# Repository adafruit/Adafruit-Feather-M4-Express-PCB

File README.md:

## Adafruit Feather M4 Express microcontroller board PCB

<a href="http://www.adafruit.com/products/3857"><br/>
Click here to purchase one from the Adafruit shop</a>

PCB files for the Adafruit Feather M4 Express. PCB format is EagleCAD schematic and board layout

For more details, check out the product pages at
* https://www.adafruit.com/products/3857

### Description

It's what you've been waiting for, the Feather M4 Express featuring ATSAMD51. This Feather is fast like a swift, smart like an owl, strong like a ox-bird (it's half ox, half bird, OK?) This feather is powered by our new favorite chip, the ATSAMD51J19 -  with its 120MHz Cortex M4 with floating point support and 512KB Flash and 192KB RAM. Your code will zig and zag and zoom, and with a bunch of extra peripherals for support, this will for sure be your favorite new chipset.

And best of all, it's a Feather - so you know it will work with all our FeatherWings! What a great way to quickly get up and running.

The most exciting part of the Feather M4 is that while you can use it with the Arduino IDE - and it's bonkers fast when you do, we are shipping it with CircuitPython on board. When you plug it in, it will show up as a very small disk drive with main.py on it. Edit main.py with your favorite text editor to build your project using Python, the most popular programming language. No installs, IDE or compiler needed, so you can use it on any computer, even ChromeBooks or computers you can't install software on. When you're done, unplug the Feather and your code will go with you.

### License

Adafruit invests time and resources providing this open source design, please support Adafruit and open-source hardware by purchasing products from [Adafruit](https://www.adafruit.com)!

Designed by Limor Fried/Ladyada for Adafruit Industries.

Creative Commons Attribution/Share-Alike, all text above must be included in any redistribution. See license.txt for additional details.

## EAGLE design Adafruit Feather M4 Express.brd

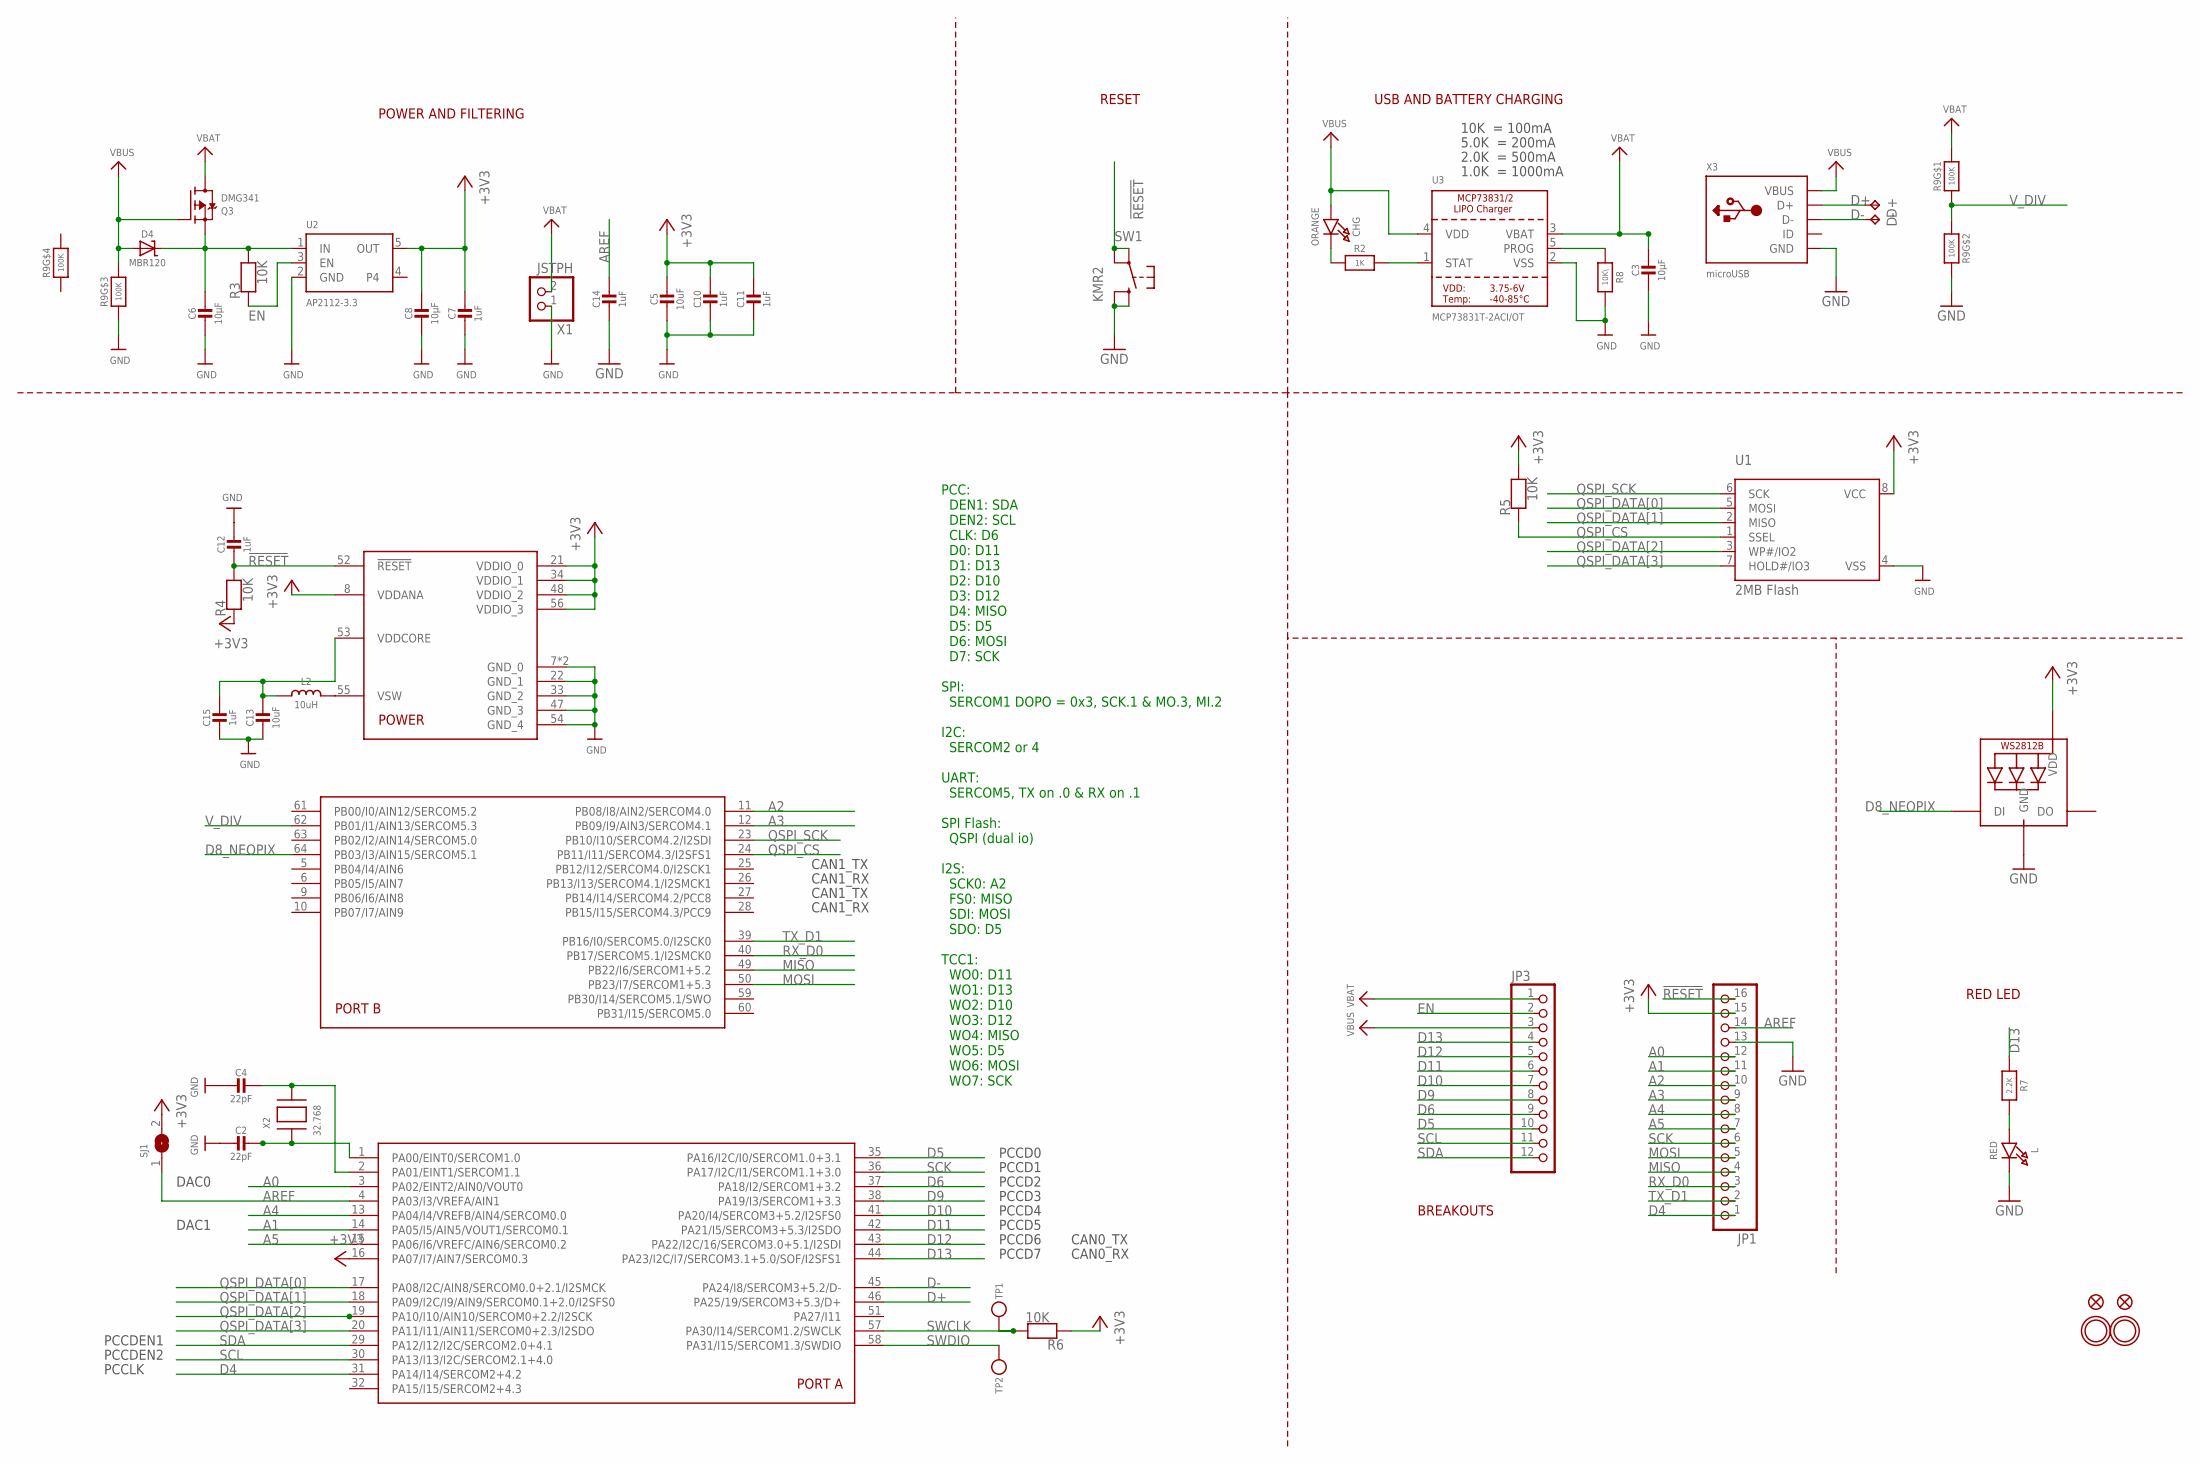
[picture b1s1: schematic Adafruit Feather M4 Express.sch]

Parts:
C2, C4: 22pF; 0603-NO
C3, C6, C8: 10µF; 0805-NO
C5, C13: 10uF; 0805-NO
C7, C10, C11, C12, C14, C15: 1uF; 0603-NO
CHG: ORANGE; CHIPLED_0805_NOOUTLINE
D4: MBR120; SOD-123
D+: TPB1,27; B1,27
D-: TPB1,27; B1,27
JP1: HEADER-1X16ROUND; 1X16_ROUND
JP3: HEADER-1X12; 1X12_ROUND
L: RED; CHIPLED_0805_NOOUTLINE
L2: 10uH; INDUCTOR_1007
LED1: WS2812B3535; LED3535
Q3: DMG341; SOT23-R
R2: 1K; 0603-NO
R3, R4, R5, R6: 10K; 0603-NO
R7: 2.2K; 0603-NO
R8: 10K\; 0603-NO
R9: 100K; RESPACK_4X0603_NO
SJ1: SOLDERJUMPERCLOSED; SOLDERJUMPER_CLOSEDWIRE
SW1: KMR2; BTN_KMR2_4.6X2.8
TP1, TP2: TESTPOINTROUND1.5MM; TESTPOINT_ROUND_1.5MM
U1: 2MB Flash; USON8
U2: AP2112-3.3; SOT23-5
U3: MCP73831T-2ACI/OT; SOT23-5
U$14: ATSAMD51J; PQFN64-1
U$31, U$32: MOUNTINGHOLE2.5; MOUNTINGHOLE_2.5_PLATED
U$34, U$35: FIDUCIAL_1MM
X1: JSTPH; JSTPH2
X2: 32.768; XTAL3215
X3: microUSB; 4UCONN_20329_V2

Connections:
!RESET: C12.2, JP1.16, R4.2, SW1.A, SW1.A' (P1), U$14.52 (!RESET)
+3V3: C5.1, C7.1, C8.1, C10.1, C11.1, JP1.15, LED1.2 (VDD), R4.1, R5.2, R6.1, SJ1.2, U1.8 (VCC), U2.5 (OUT), U$14.8 (VDDANA), U$14.16 (PA07/I7/AIN7/SERCOM0.3), U$14.21 (VDDIO_0), U$14.34 (VDDIO_1), U$14.48 (VDDIO_2), U$14.56 (VDDIO_3)
A0: JP1.12, U$14.3 (PA02/EINT2/AIN0/VOUT0)
A1: JP1.11, U$14.14 (PA05/I5/AIN5/VOUT1/SERCOM0.1)
A2: JP1.10, U$14.11 (PB08/I8/AIN2/SERCOM4.0)
A3: JP1.9, U$14.12 (PB09/I9/AIN3/SERCOM4.1)
A4: JP1.8, U$14.13 (PA04/I4/VREFB/AIN4/SERCOM0.0)
A5: JP1.7, U$14.15 (PA06/I6/VREFC/AIN6/SERCOM0.2)
AREF: C14.1, JP1.14, SJ1.1, U$14.4 (PA03/I3/VREFA/AIN1)
D4: JP1.1, U$14.31 (PA14/I14/SERCOM2+4.2)
D5: JP3.10, U$14.35 (PA16/I2C/I0/SERCOM1.0+3.1)
D6: JP3.9, U$14.37 (PA18/I2/SERCOM1+3.2)
D8_NEOPIX: LED1.1 (DI), U$14.64 (PB03/I3/AIN15/SERCOM5.1)
D9: JP3.8, U$14.38 (PA19/I3/SERCOM1+3.3)
D10: JP3.7, U$14.41 (PA20/I4/SERCOM3+5.2/I2SFS0)
D11: JP3.6, U$14.42 (PA21/I5/SERCOM3+5.3/I2SDO)
D12: JP3.5, U$14.43 (PA22/I2C/16/SERCOM3.0+5.1/I2SDI)
D13: JP3.4, R7.1, U$14.44 (PA23/I2C/I7/SERCOM3.1+5.0/SOF/I2SFS1)
D+: D+.TP, U$14.46 (PA25/19/SERCOM3+5.3/D+), X3.D+
D-: D-.TP, U$14.45 (PA24/I8/SERCOM3+5.2/D-), X3.D-
EN: JP3.2, R3.1, U2.3 (EN)
GND: C2.2, C3.2, C4.2, C5.2, C6.2, C7.2, C8.2, C10.2, C11.2, C12.1, C13.2, C14.2, C15.2, JP1.13, L.C, LED1.4 (GND), R8.2, R9.3 (1), R9.7 (2), SW1.B (S), SW1.B' (S1), U1.4 (VSS), U2.2 (GND), U3.2 (VSS), U$14.7 (GND_0), U$14.22 (GND_1), U$14.33 (GND_2), U$14.47 (GND_3), U$14.54 (GND_4), U$14.EXP (GND_0), X1.1, X3.BASE@1 (GND), X3.BASE@2 (GND), X3.GND, X3.SPRT@1 (GND), X3.SPRT@2 (GND), X3.SPRT@3 (GND), X3.SPRT@4 (GND)
MISO: JP1.4, U$14.49 (PB22/I6/SERCOM1+5.2)
MOSI: JP1.5, U$14.50 (PB23/I7/SERCOM1+5.3)
unnamed: CHG.C, R2.1
unnamed: L.A, R7.2
unnamed: R2.2, U3.1 (STAT)
unnamed: R8.1, U3.5 (PROG)
unnamed: C2.1, U$14.1 (PA00/EINT0/SERCOM1.0), X2.P$1
unnamed: C4.1, U$14.2 (PA01/EINT1/SERCOM1.1), X2.P$2
unnamed: L2.P$2 (2), U$14.55 (VSW)
QSPI_CS: R5.1, U1.1 (SSEL), U$14.24 (PB11/I11/SERCOM4.3/I2SFS1)
QSPI_DATA[0]: U1.5 (MOSI), U$14.17 (PA08/I2C/AIN8/SERCOM0.0+2.1/I2SMCK)
QSPI_DATA[1]: U1.2 (MISO), U$14.18 (PA09/I2C/I9/AIN9/SERCOM0.1+2.0/I2SFS0)
QSPI_DATA[2]: U1.3 (WP#/IO2), U$14.19 (PA10/I10/AIN10/SERCOM0+2.2/I2SCK)
QSPI_DATA[3]: U1.7 (HOLD#/IO3), U$14.20 (PA11/I11/AIN11/SERCOM0+2.3/I2SDO)
QSPI_SCK: U1.6 (SCK), U$14.23 (PB10/I10/SERCOM4.2/I2SDI)
RX_D0: JP1.3, U$14.40 (PB17/SERCOM5.1/I2SMCK0)
SCK: JP1.6, U$14.36 (PA17/I2C/I1/SERCOM1.1+3.0)
SCL: JP3.11, U$14.30 (PA13/I13/I2C/SERCOM2.1+4.0)
SDA: JP3.12, U$14.29 (PA12/I12/I2C/SERCOM2.0+4.1)
SWCLK: R6.2, TP1.P$1, U$14.57 (PA30/I14/SERCOM1.2/SWCLK)
SWDIO: TP2.P$1, U$14.58 (PA31/I15/SERCOM1.3/SWDIO)
TX_D1: JP1.2, U$14.39 (PB16/I0/SERCOM5.0/I2SCK0)
VBAT: C3.1, JP3.1, Q3.3 (D), R9.8 (2), U3.3 (VBAT), X1.2
VBUS: CHG.A, D4.A, JP3.3, Q3.1 (G), R9.6 (2), U3.4 (VDD), X3.VBUS
VDDCORE1: C13.1, C15.1, L2.P$1 (1), U$14.53 (VDDCORE)
VHI: C6.1, D4.C, Q3.2 (S), R3.2, U2.1 (IN)
V_DIV: R9.1, R9.2 (1), U$14.62 (PB01/I1/AIN13/SERCOM5.3)

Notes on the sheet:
POWER AND FILTERING
RESET
10K = 100mA
5.0K = 200mA
2.0K = 500mA
1.0K = 1000mA
USB AND BATTERY CHARGING
BREAKOUTS
RED LED
PCCDEN1
PCCDEN2
PCCD0
PCCD1
PCCD2
PCCD3
PCCD4
PCCD5
PCCD6
PCCD7
PCCLK
PCC: DEN1: SDA DEN2: SCL CLK: D6 D0: D11 D1: D13 D2: D10 D3: D12 D4: MISO D5: D5 D6: MOSI D7: SCK SPI: SERCOM1 DOPO = 0x3, SCK.1 & MO.3, MI.2 I2C: SERCOM2 or 4 UART: SERCOM5, TX on .0 & RX on .1 SPI Flash: QSPI (dual io) I2S: SCK0: A2 FS0: MISO SDI: MOSI SDO: D5 TCC1: WO0: D11 WO1: D13 WO2: D10 WO3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
CAN0_TX
CAN0_RX
DAC0
DAC1
CAN1_TX
CAN1_RX

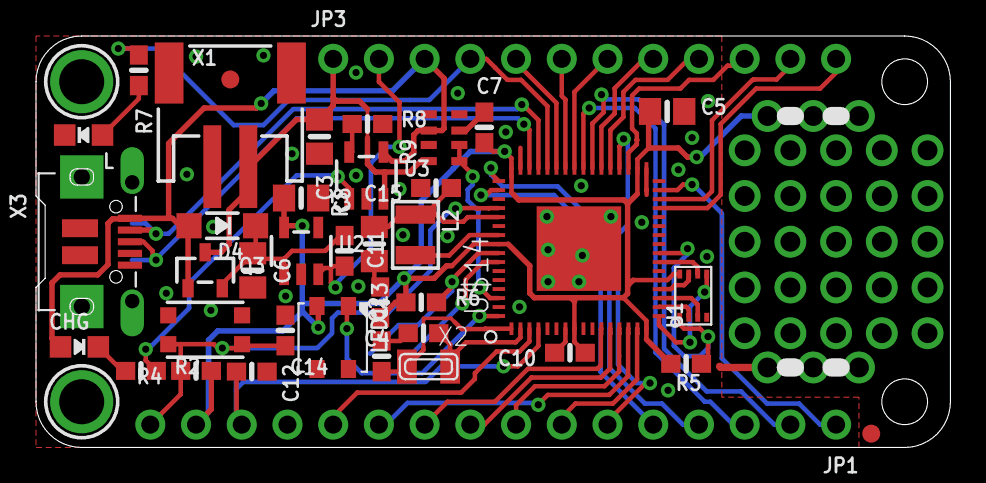
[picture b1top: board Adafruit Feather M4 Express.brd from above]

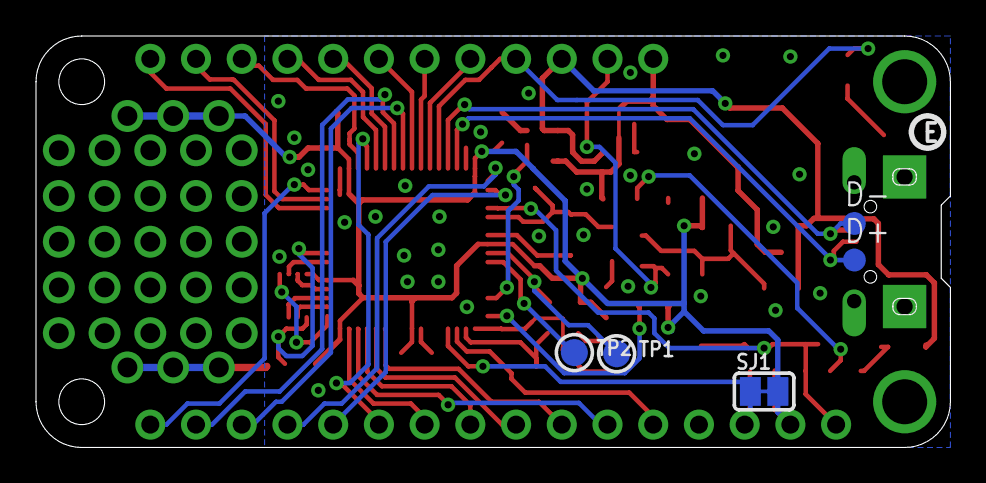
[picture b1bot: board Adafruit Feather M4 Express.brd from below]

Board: 2 copper layers, 50.8 x 22.9 mm, 49 parts (7 on the bottom side), 49 nets.

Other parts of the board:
U$5: FEATHERM4_BOT
U$6: FEATHERM4_TOP
U$13: PCBFEAT-REV-040

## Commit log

2018-07-08 init
2022-04-27 Added Prettypins
2022-04-27 Deleted file to rename
2022-04-27 Added PrettyPins again

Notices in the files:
parts and their libraries:
microbuilder: This work is placed in the public domain, and may be freely used for commercial and non-commercial work with the following conditions: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
